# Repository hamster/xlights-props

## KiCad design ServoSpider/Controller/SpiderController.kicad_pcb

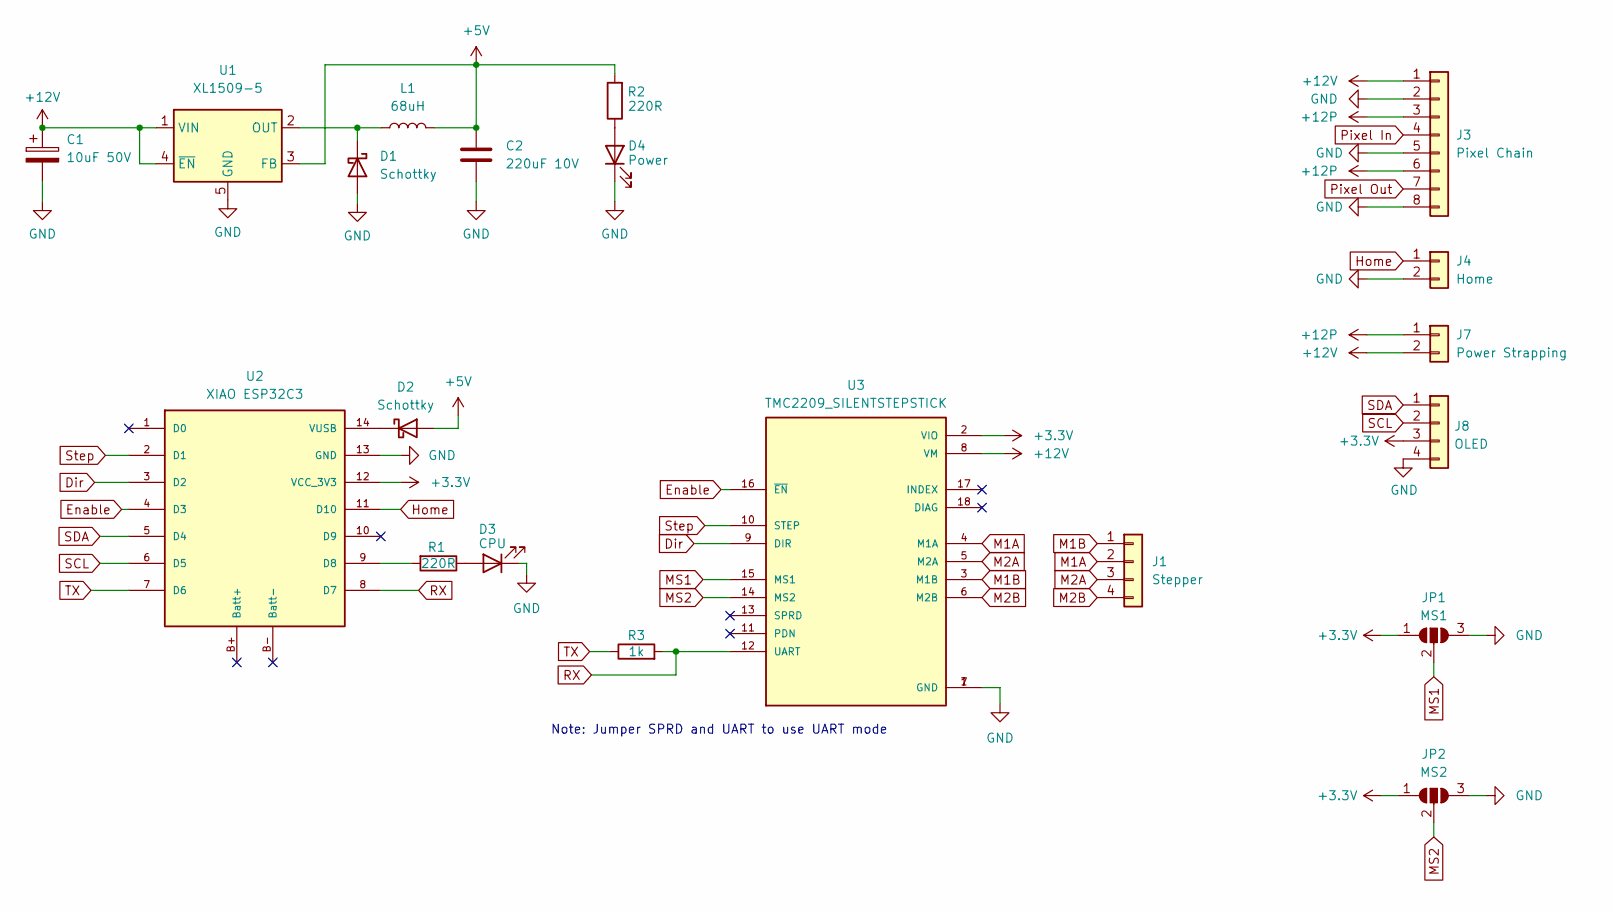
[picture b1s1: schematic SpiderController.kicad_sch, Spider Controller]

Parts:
C1: 10uF 50V; C_1206_3216Metric
C2: 220uF 10V; CP_EIA-7343-15_Kemet-W_HandSolder
D1, D2: Schottky; D_SOD-123F
D3: CPU; LED_0805_2012Metric
D4: Power; LED_0805_2012Metric
J1: Stepper; JST_EH_B4B-EH-A_1x04_P2.50mm_Vertical
J3: Pixel Chain; QT5.0-8
J4: Home; JST_EH_B2B-EH-A_1x02_P2.50mm_Vertical
J7: Power Strapping; PinHeader_1x02_P2.54mm_Vertical
J8: OLED; PinHeader_1x04_P2.54mm_Vertical
JP1: MS1; SolderJumper-3_P1.3mm_Open_RoundedPad1.0x1.5mm
JP2: MS2; SolderJumper-3_P1.3mm_Open_RoundedPad1.0x1.5mm
L1: 68uH; L_Taiyo-Yuden_MD-5050
R1, R2: 220R; R_0603_1608Metric
R3: 1k; R_0603_1608Metric
U1: XL1509-5; SOIC-8_3.9x4.9mm_P1.27mm
U2: XIAO ESP32C3; xiao_esp32c3
U3: TMC2209_SILENTSTEPSTICK; MODULE_TMC2209_SILENTSTEPSTICK; PARTREV 1.20

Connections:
+3.3V: J8.3, JP1.1 (A), JP2.1 (A), U2.12 (VCC_3V3), U3.2 (VIO)
+5V: C2.1, D2.2 (A), L1.2, R2.2, U1.3 (FB)
+12P: J3.3, J3.6, J7.1
+12V: C1.1, J3.1, J7.2, U1.1 (VIN), U1.4 (~EN), U3.8 (VM)
Dir: U2.3 (D2), U3.9 (DIR)
Enable: U2.4 (D3), U3.16 (~EN)
GND: C1.2, C2.2, D1.2 (A), D3.1 (K), D4.1 (K), J3.2, J3.5, J3.8, J4.2, J8.4, JP1.3 (B), JP2.3 (B), U1.5 (GND), U1.6 (GND), U1.7 (GND), U1.8 (GND), U2.13 (GND), U3.1 (GND), U3.7 (GND)
Home: J4.1, U2.11 (D10)
M1A: J1.2, U3.4 (M1A)
M1B: J1.1, U3.3 (M1B)
M2A: J1.3, U3.5 (M2A)
M2B: J1.4, U3.6 (M2B)
MS1: JP1.2 (C), U3.15 (MS1)
MS2: JP2.2 (C), U3.14 (MS2)
unnamed: D1.1 (K), L1.1, U1.2 (OUT)
unnamed: D2.1 (K), U2.14 (VUSB)
unnamed: D3.2 (A), R1.1
unnamed: D4.2 (A), R2.1
unnamed: R1.2, U2.9 (D8)
Pixel In: J3.4
Pixel Out: J3.7
RX: R3.2, U2.8 (D7), U3.12 (UART)
SCL: J8.2, U2.6 (D5)
SDA: J8.1, U2.5 (D4)
Step: U2.2 (D1), U3.10 (STEP)
TX: R3.1, U2.7 (D6)

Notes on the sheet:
Note: Jumper SPRD and UART to use UART mode

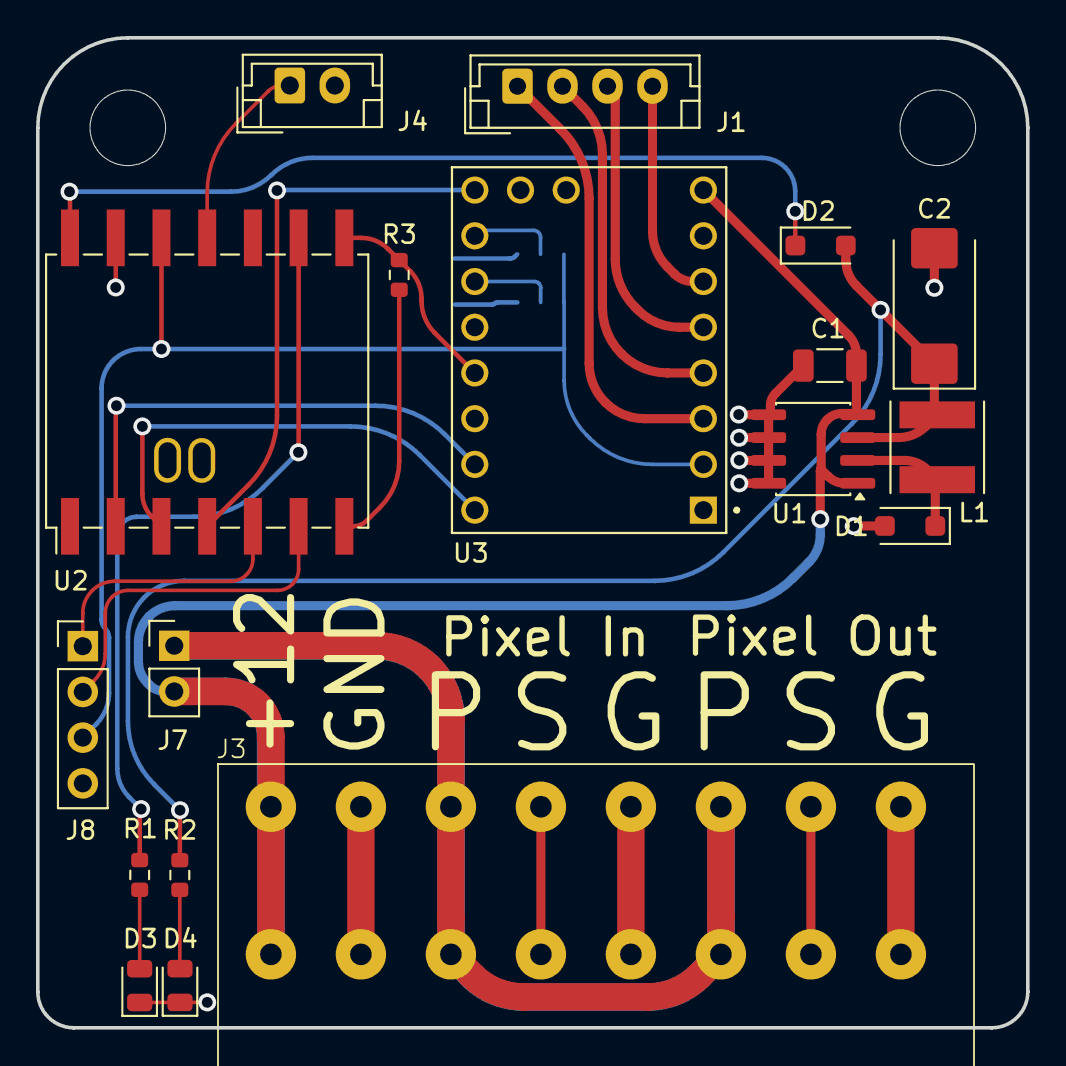
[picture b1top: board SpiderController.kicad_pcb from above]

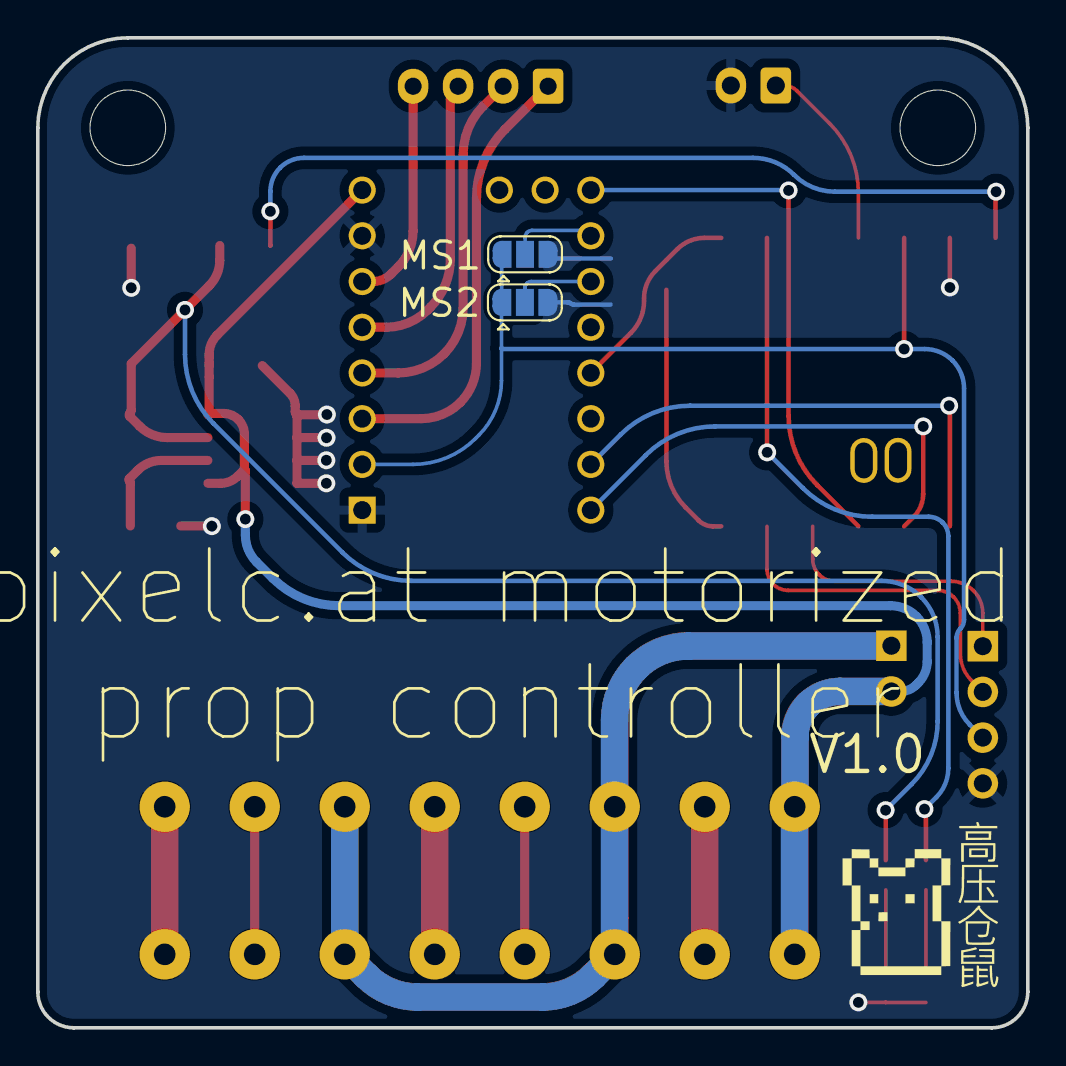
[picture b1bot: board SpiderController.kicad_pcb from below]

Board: 2 copper layers, 55.0 x 55.0 mm, 20 parts (2 on the bottom side), 24 nets.

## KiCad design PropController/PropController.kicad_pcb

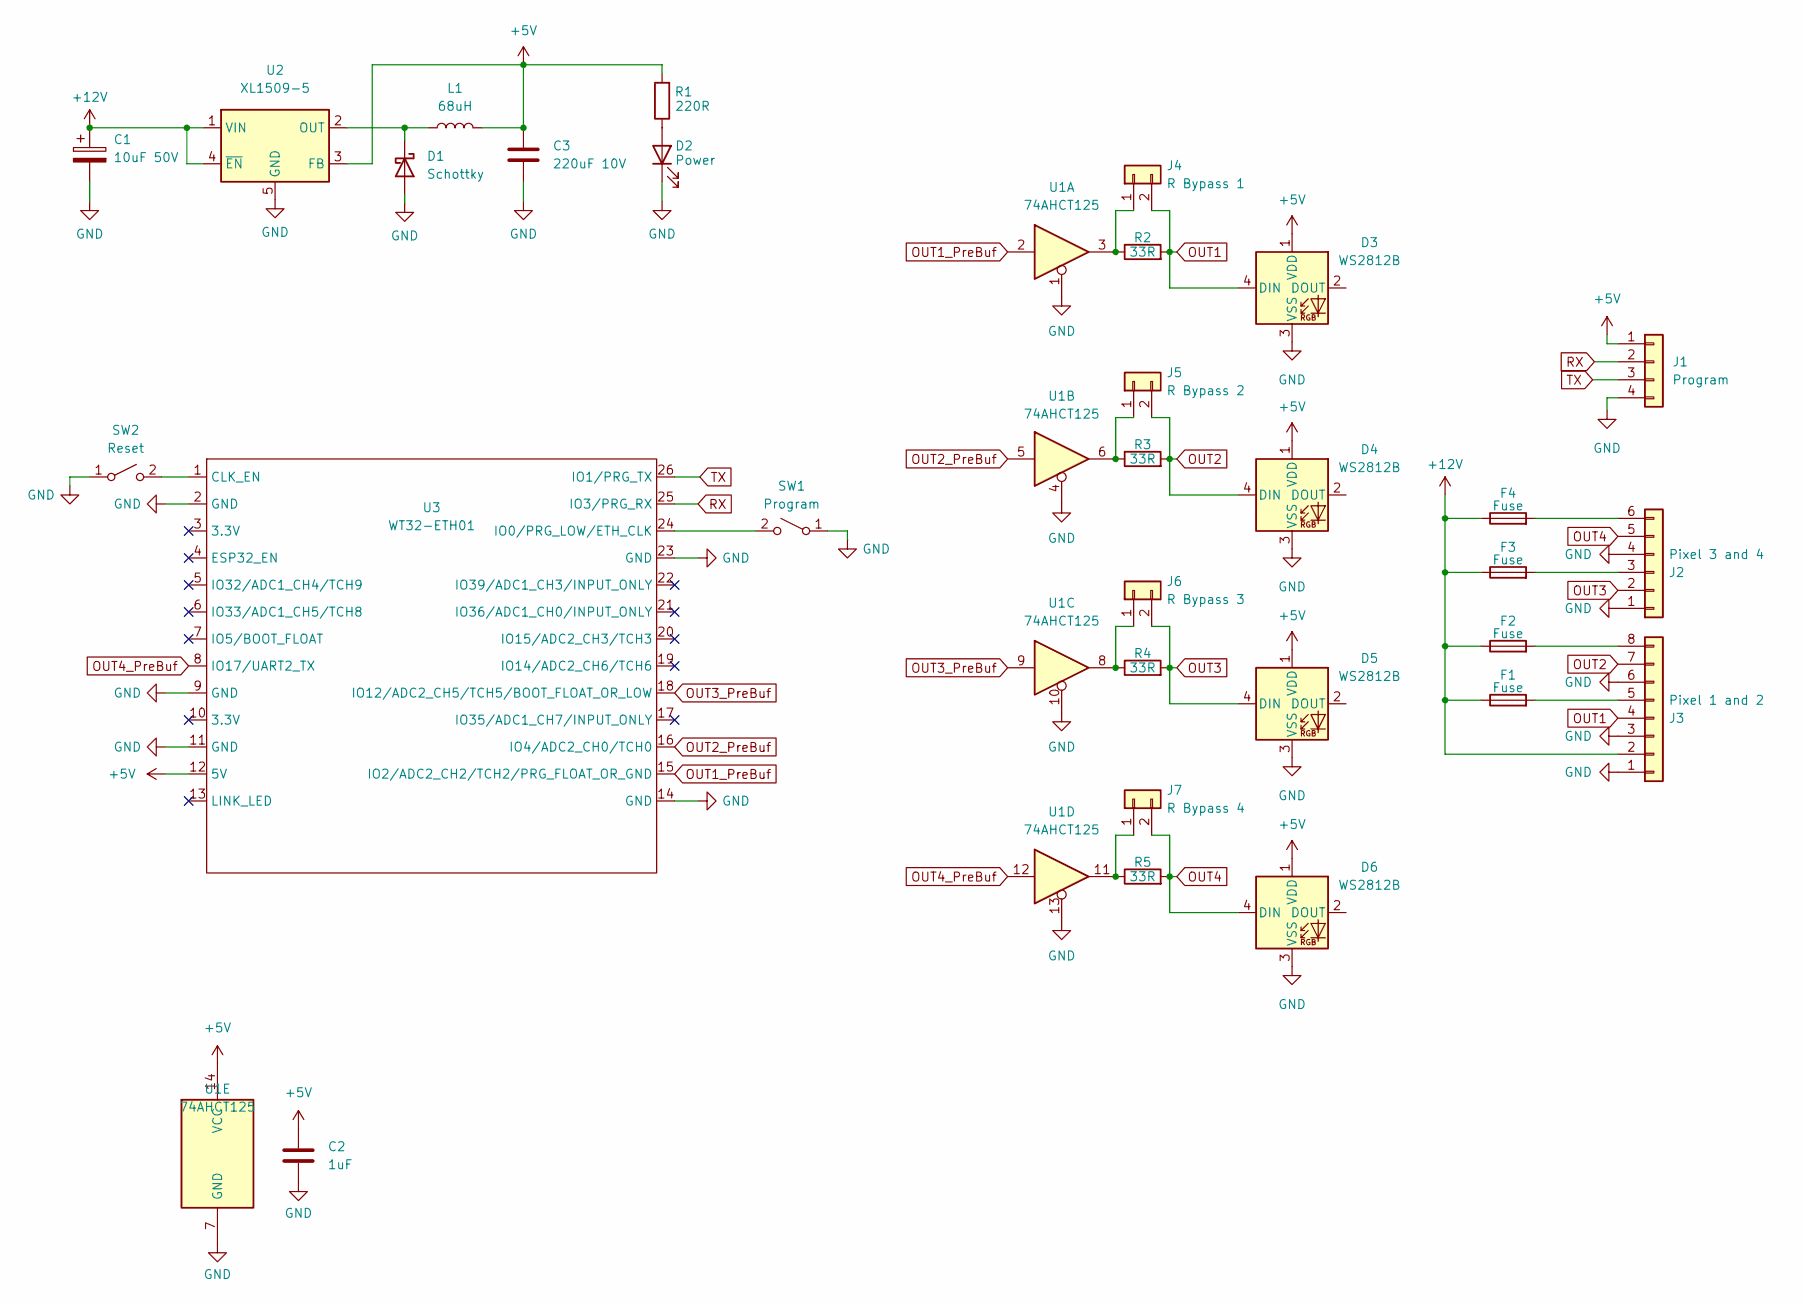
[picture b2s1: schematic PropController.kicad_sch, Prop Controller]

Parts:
C1: 10uF 50V; C_1206_3216Metric
C2: 1uF; C_0603_1608Metric
C3: 220uF 10V; CP_EIA-7343-15_Kemet-W_HandSolder
D1: Schottky; D_SOD-123F
D2: Power; LED_0805_2012Metric
D3, D4, D5, D6: WS2812B; LED_WS2812B_PLCC4_5.0x5.0mm_P3.2mm
F1, F2, F3, F4: Fuse; Fuseholder_Blade_Mini_Keystone_3568
J1: Program; PinHeader_1x04_P2.54mm_Vertical
J2: Pixel 3 and 4; QT5.0-6
J3: Pixel 1 and 2; QT5.0-8
J4: R Bypass 1; PinHeader_1x02_P2.54mm_Vertical
J5: R Bypass 2; PinHeader_1x02_P2.54mm_Vertical
J6: R Bypass 3; PinHeader_1x02_P2.54mm_Vertical
J7: R Bypass 4; PinHeader_1x02_P2.54mm_Vertical
L1: 68uH; L_Taiyo-Yuden_MD-5050
R1: 220R; R_0603_1608Metric
R2, R3, R4, R5: 33R; R_0603_1608Metric
SW1: Program; SW_SPST_EVPBF
SW2: Reset; SW_SPST_EVPBF
U1: 74AHCT125; SOIC-14_3.9x8.7mm_P1.27mm
U2: XL1509-5; SOIC-8_3.9x4.9mm_P1.27mm
U3: WT32-ETH01

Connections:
+5V: C2.1, C3.1, D3.1 (VDD), D4.1 (VDD), D5.1 (VDD), D6.1 (VDD), J1.1, L1.2, R1.2, U1.14 (VCC), U2.3 (FB), U3.12 (5V)
+12V: C1.1, F1.1, F2.1, F3.1, F4.1, J3.2, U2.1 (VIN), U2.4 (~EN)
GND: C1.2, C2.2, C3.2, D1.2 (A), D2.1 (K), D3.3 (VSS), D4.3 (VSS), D5.3 (VSS), D6.3 (VSS), J1.4, J2.1, J2.4, J3.1, J3.3, J3.6, SW1.1 (A), SW2.1 (A), U1.1, U1.4, U1.7 (GND), U1.10, U1.13, U2.5 (GND), U2.6 (GND), U2.7 (GND), U2.8 (GND), U3.2 (GND), U3.9 (GND), U3.11 (GND), U3.14 (GND), U3.23 (GND)
unnamed: D1.1 (K), L1.1, U2.2 (OUT)
unnamed: D2.2 (A), R1.1
unnamed: F3.2, J2.3
unnamed: F4.2, J2.6
unnamed: F1.2, J3.5
unnamed: F2.2, J3.8
unnamed: J4.1, R2.1, U1.3
unnamed: J5.1, R3.1, U1.6
unnamed: J6.1, R4.1, U1.8
unnamed: J7.1, R5.1, U1.11
unnamed: SW1.2 (B), U3.24 (IO0/PRG_LOW/ETH_CLK)
unnamed: SW2.2 (B), U3.1 (CLK_EN)
OUT1: D3.4 (DIN), J3.4, J4.2, R2.2
OUT1_PreBuf: U1.2, U3.15 (IO2/ADC2_CH2/TCH2/PRG_FLOAT_OR_GND)
OUT2: D4.4 (DIN), J3.7, J5.2, R3.2
OUT2_PreBuf: U1.5, U3.16 (IO4/ADC2_CH0/TCH0)
OUT3: D5.4 (DIN), J2.2, J6.2, R4.2
OUT3_PreBuf: U1.9, U3.18 (IO12/ADC2_CH5/TCH5/BOOT_FLOAT_OR_LOW)
OUT4: D6.4 (DIN), J2.5, J7.2, R5.2
OUT4_PreBuf: U1.12, U3.8 (IO17/UART2_TX)
RX: J1.2, U3.25 (IO3/PRG_RX)
TX: J1.3, U3.26 (IO1/PRG_TX)

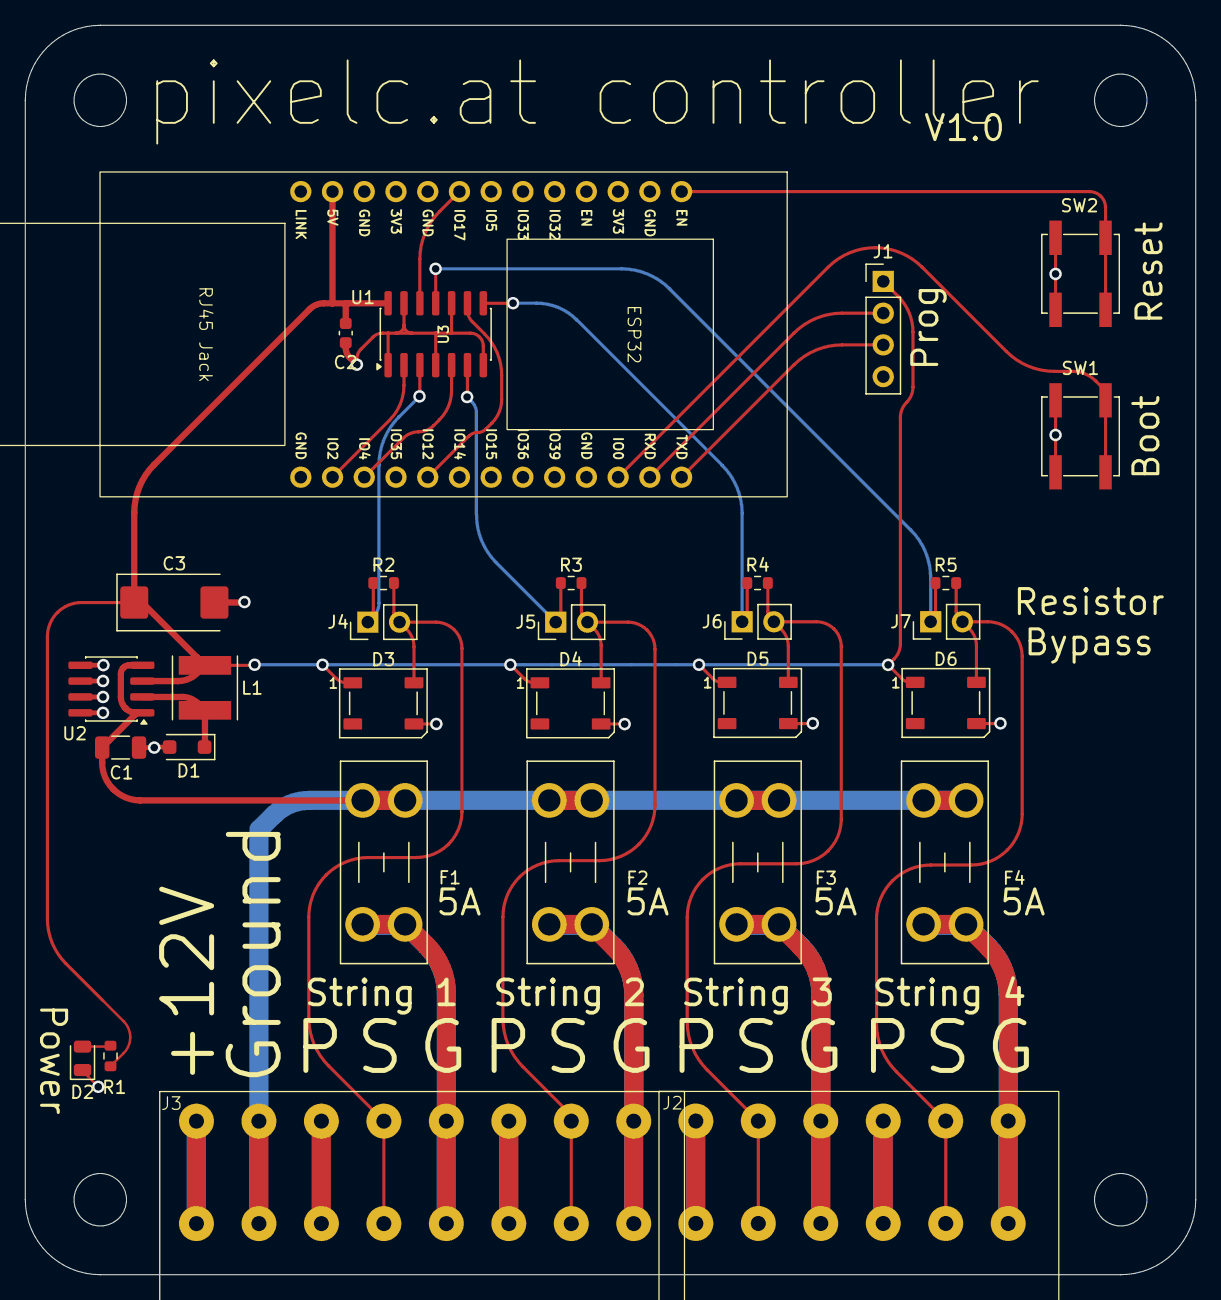
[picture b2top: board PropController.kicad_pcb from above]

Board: 2 copper layers, 93.7 x 100.0 mm, 31 parts (0 on the bottom side), 25 nets.

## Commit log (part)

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2025-10-30 Adding PEX connnector Update Tombstone Matrix model for the zig-zag of the matrix
2025-11-01 Adding ServoController
2025-12-28 Adding Really Big Bulb seed pixel holder
2025-12-28 Adding snowflake design
2025-12-28 Adding small large bulb holder Updating the spider mount
2025-12-28 Updating the prop mount system to be detachable
2025-12-28 Updated the ServoController to have a pretty complete webpage and implementation. OTA is still broken.
2025-12-28 Fixed OTA Updated README
2025-12-28 Updated README for real
2025-12-30 Supports 16 bit or 8 bit mode Added some new serial commands Added reset button OTA updates work
